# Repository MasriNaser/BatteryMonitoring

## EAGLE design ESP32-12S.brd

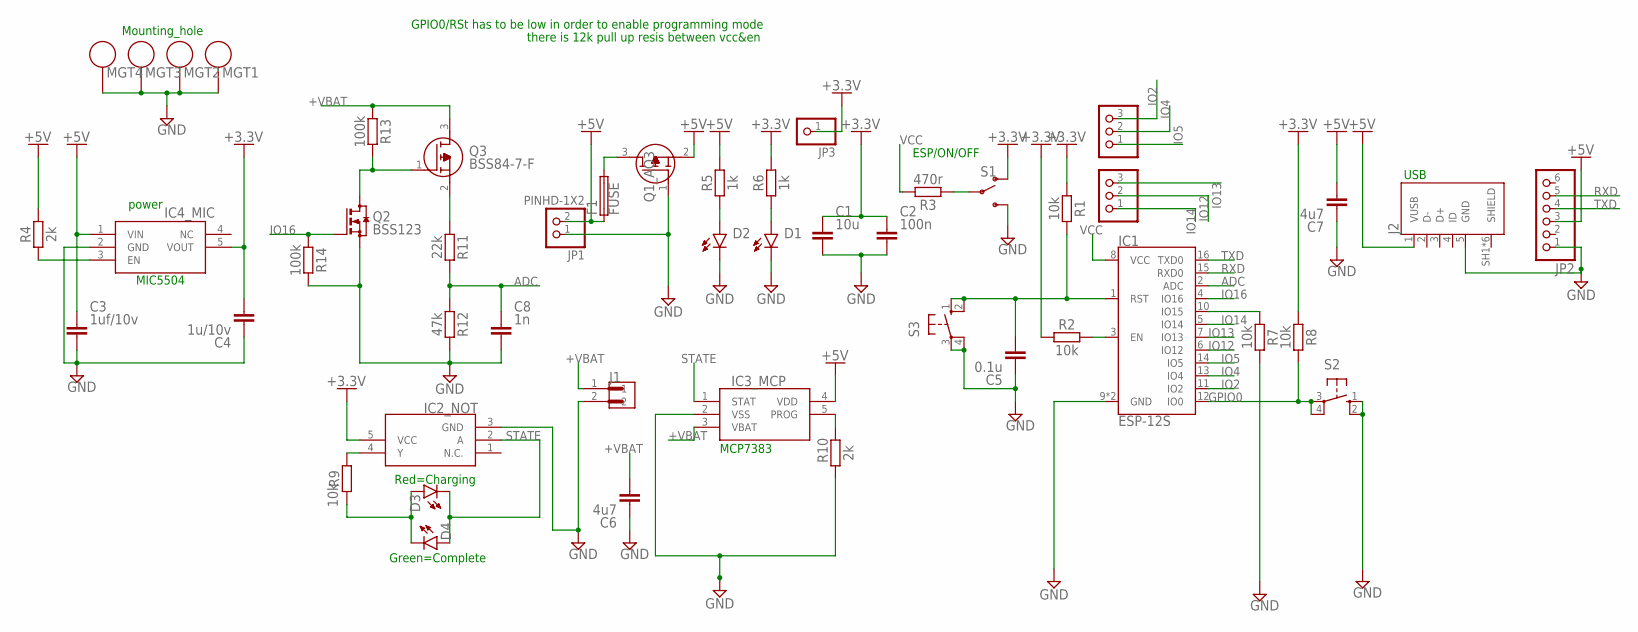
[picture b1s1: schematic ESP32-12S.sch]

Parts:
C1: 10u; CAPC1608X85
C2: 100n; CAPC1608X85
C3: 1uf/10v; CAPC2012X110
C4: 1u/10v; CAPC2012X110
C5: 0.1u; CAPC1608X85
C6, C7: 4u7; CAPC1608X85
C8: 1n; CAPC1608X85
D1, D2, D3, D4: CHIP-ROUND-R_0805; LEDC2012X105N_RND-R
F1: FUSE; FUSC1608X60N
IC1: ESP-12S
IC2_NOT: 74HC1G04GW,125; SOT65P212X110-5N
IC3_MCP: MCP73831T-2ATI_OT; SOT95P270X145-5N
IC4_MIC: MIC5504-3.3YM5-TR; SOT95P280X145-5N
J1: S2B-XH-A(LF)(SN); JST_S2B-XH-A(LF)(SN)
J2: 10118192-0001LF; AMPHENOL_10118192-0001LF
JP1: PINHD-1X2; 1X02
JP2: PINHD-1X6; 1X06
JP3: PINHD-1X1; 1X01
JP4, JP5: PINHD-1X3; 1X03
MGT1, MGT2, MGT3, MGT4: BEAGLEBONEBLACK_MOUNTING_HOLE
Q1_AO3: AO3401A; SOT95P280X125-3N
Q2: BSS123; SOT23
Q3: BSS84-7-F; SOT96P240X110-3N
R1, R2, R7, R8, R9: 10k; RESC1608X60
R3: 470r; RESC1608X60
R4, R10: 2k; RESC1608X60
R5, R6: 1k; RESC1608X60
R11: 22k; RESC3216X70
R12: 47k; RESC3216X70
R13, R14: 100k; RESC3216X70
S1: SWITCH-SPDT-SMD-RIGHT-ANGLE; SWITCH_SPST_SMD_A
S2, S3: 10-XX; B3F-10XX

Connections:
+3.3V: C1.1, C2.1, C4.2, IC2_NOT.5 (VCC), IC4_MIC.5 (VOUT), JP3.1, R1.1, R2.1, R6.2, R8.1, S1.1 (O)
+5V: C3.1, C7.2, F1.1, IC3_MCP.4 (VDD), IC4_MIC.1 (VIN), J2.1 (VUSB), JP1.2, JP2.3, Q1_AO3.2 (S), R4.2, R5.2
+VBAT: C6.2, IC3_MCP.3 (VBAT), J1.1, Q3.3 (D), R13.1
ADC: C8.1, IC1.2 (ADC), R11.2, R12.1
GND: C1.2, C2.2, C3.2, C4.1, C5.1, C6.1, C7.1, C8.2, D1.C, D2.C, IC1.9 (GND), IC1.P$1 (GND), IC2_NOT.3 (GND), IC3_MCP.2 (VSS), IC4_MIC.2 (GND), J1.2, J2.5 (GND), JP1.1, JP2.1, MGT1.P$1, MGT2.P$1, MGT3.P$1, MGT4.P$1, Q1_AO3.1 (G), Q2.2 (S), R7.2, R10.1, R12.2, R14.2, S1.3 (S), S2.1 (S), S2.2 (S1), S3.3, S3.4 (P1)
GPIO0: IC1.12 (IO0), R8.2, S2.3, S2.4 (P1)
IO2: IC1.11 (IO2), JP4.3
IO4: IC1.13 (IO4), JP4.2
IO5: IC1.14 (IO5), JP4.1
IO12: IC1.6 (IO12), JP5.2
IO13: IC1.7 (IO13), JP5.3
IO14: IC1.5 (IO14), JP5.1
IO16: IC1.4 (IO16), Q2.1 (G), R14.1
unnamed: IC1.3 (EN), R2.2
unnamed: IC4_MIC.3 (EN), R4.1
unnamed: D1.A, R6.1
unnamed: D2.A, R5.1
unnamed: IC1.10 (IO15), R7.1
unnamed: F1.2, Q1_AO3.3 (D)
unnamed: IC3_MCP.5 (PROG), R10.2
unnamed: R3.1, S1.2
unnamed: Q3.2 (S), R11.1
unnamed: IC2_NOT.4 (Y), R9.2
unnamed: D3.A, D4.C, R9.1
unnamed: Q2.3 (D), Q3.1 (G), R13.2
RST: C5.2, IC1.1 (RST), R1.2, S3.1 (S), S3.2 (S1)
RXD: IC1.15 (RXD0), JP2.5
STATE: D3.C, D4.A, IC2_NOT.2 (A), IC3_MCP.1 (STAT)
TXD: IC1.16 (TXD0), JP2.4
VCC: IC1.8 (VCC), R3.2

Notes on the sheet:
there is 12k pull up resis between vcc&en
GPIO0/RSt has to be low in order to enable programming mode
power
MIC5504
MCP7383
USB
Mounting_hole
Green=Complete
Red=Charging
ESP/ON/OFF

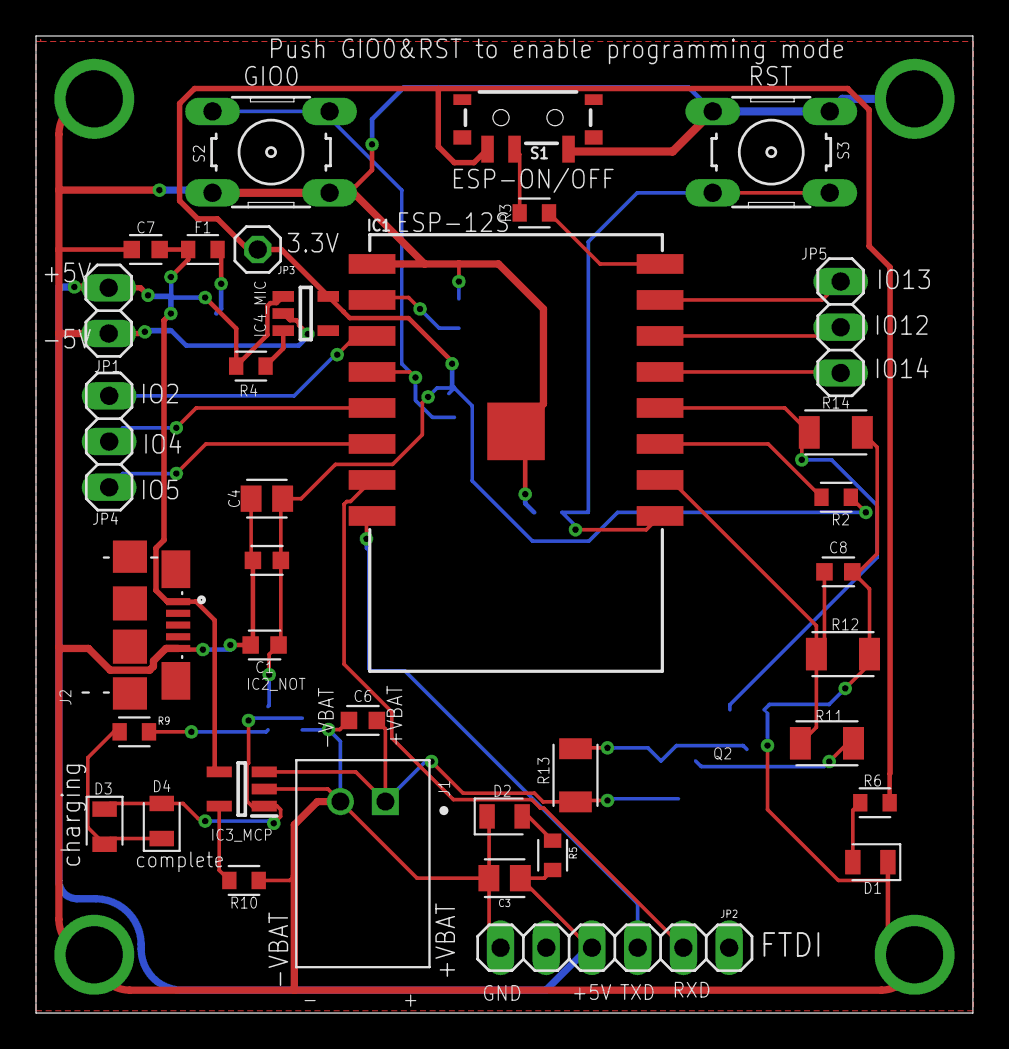
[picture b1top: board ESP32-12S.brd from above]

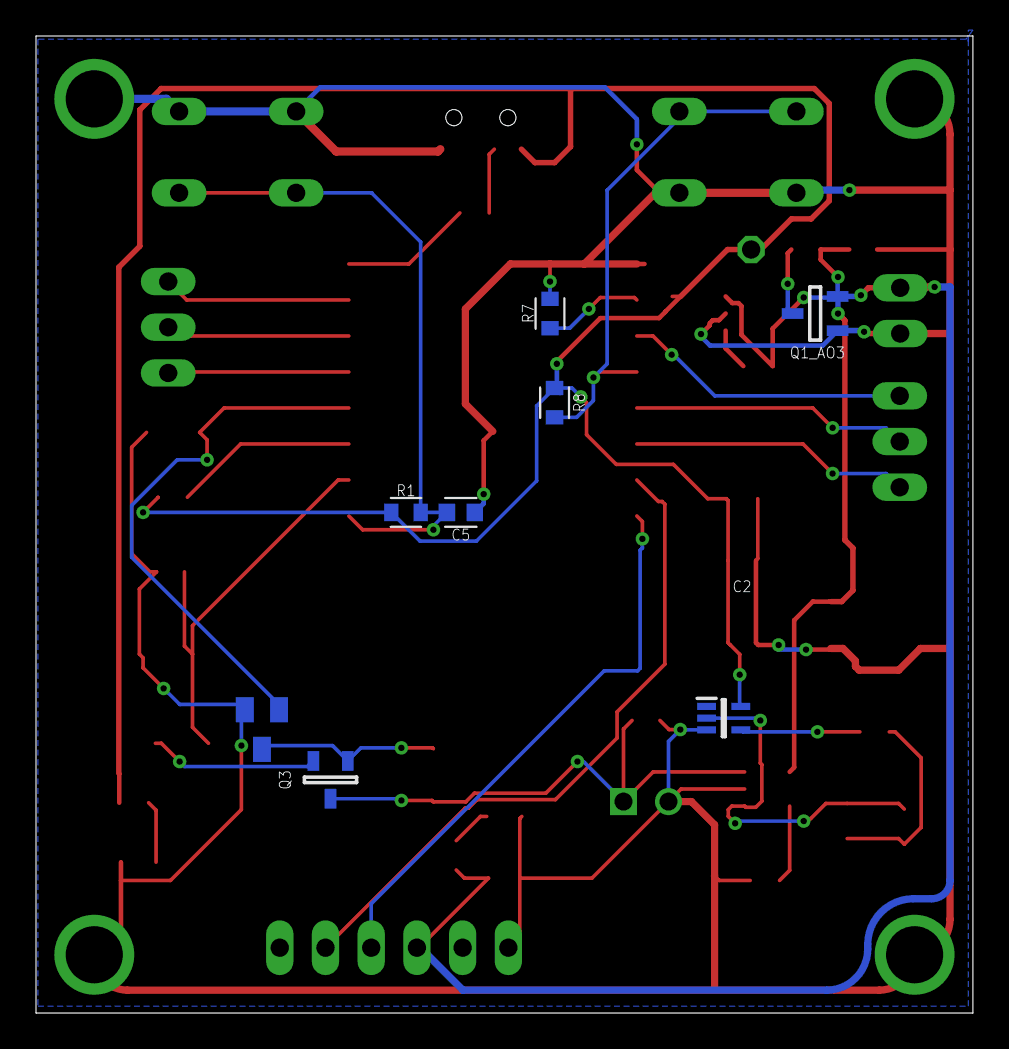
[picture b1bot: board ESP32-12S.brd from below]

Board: 2 copper layers, 52.0 x 54.3 mm, 48 parts (8 on the bottom side), 30 nets.

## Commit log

2021-04-22 battery monitoring
2021-04-26 add gerber file
